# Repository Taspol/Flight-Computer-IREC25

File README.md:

## Link for Pin out Stm32Cube IDE
- https://drive.google.com/drive/folders/1xgfmS8LAHjObwQE3LNUNcHKHxMRXHLm3?usp=drive_link
# Flight Computer
## Overview
The Flight Computer is an embedded system designed for real-time data acquisition, processing, and communication in aerospace applications. It integrates multiple sensors and communication modules using an STM32 microcontroller, making it suitable for rocket flight.
## Features
**EnvSensor**
  - ADXL375BCCZ-RL7 (High-G Accelerometer)
  - BMI088 (Low-G Accelerometer & IMU Gyroscope)
  - MMC5983MA (Magnetometer)
  - TMP275AIDGKR VSSOP8 (OnBoard Temperature Sensors)
  - MS5607-02BA (Altimeter)

**Communication Modules**
  - SX1262 (Lora Module)

**Localization Modules**
  - SAM-M10Q (GNSS Module)

**Flight Data Storage**
  - KLM8G1GETF-B041(EMMC)

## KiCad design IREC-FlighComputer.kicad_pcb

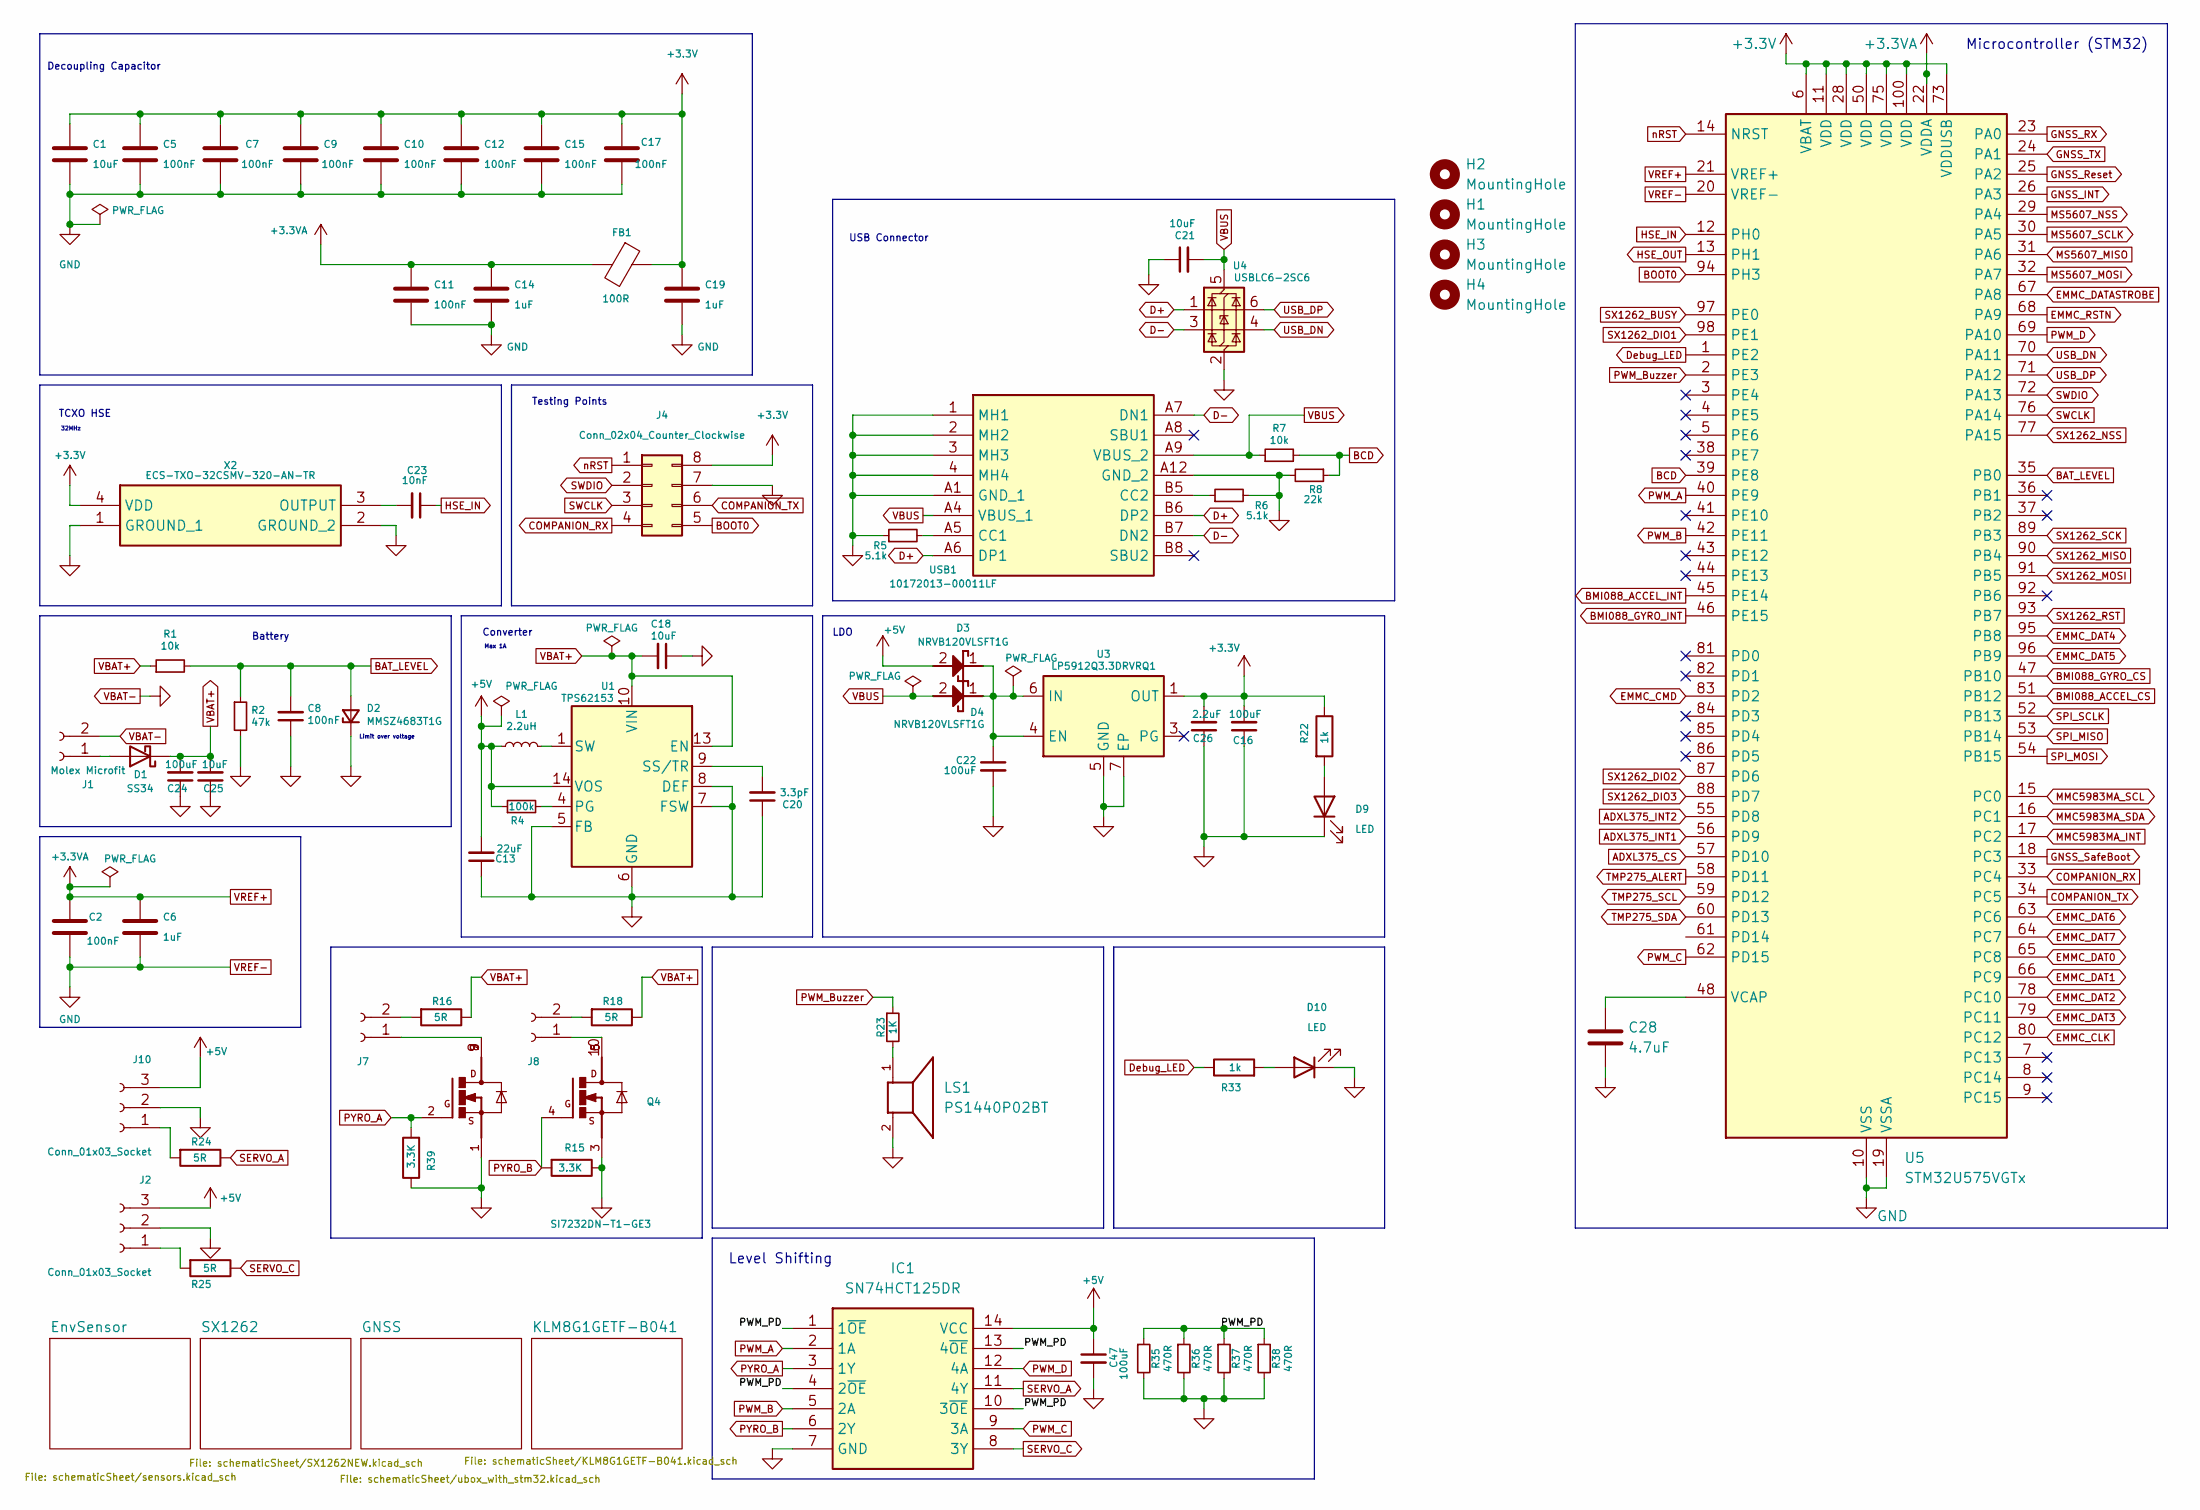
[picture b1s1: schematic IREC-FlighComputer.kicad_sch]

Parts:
C1, C18, C21, C25: 10uF; C_0402_1005Metric_Pad0.74x0.62mm_HandSolder
C2, C5, C7, C8, C9, C10, C11, C12, C15, C17: 100nF; C_0402_1005Metric_Pad0.74x0.62mm_HandSolder
C6, C14, C19: 1uF; C_0402_1005Metric_Pad0.74x0.62mm_HandSolder
C13: 22uF; C_0402_1005Metric_Pad0.74x0.62mm_HandSolder
C16, C22, C24, C47: 100uF; C_0402_1005Metric_Pad0.74x0.62mm_HandSolder
C20: 3.3pF; C_0402_1005Metric_Pad0.74x0.62mm_HandSolder
C23: 10nF; C_0402_1005Metric_Pad0.74x0.62mm_HandSolder
C26: 2.2uF; C_0402_1005Metric_Pad0.74x0.62mm_HandSolder
C28: 4.7uF; C_0402_1005Metric_Pad0.74x0.62mm_HandSolder
D1: SS34; DIOM7959X262N
D2: MMSZ4683T1G; SOD3716X135N; Manufacturer_Part_Number MMSZ4683T1G; Mouser Part Number 863-MMSZ4683T1G
D3, D4: NRVB120VLSFT1G; SODFL3616X98N; Manufacturer_Part_Number NRVB120VLSFT1G; Mouser 863-NRVB120VLSFT1G
D9, D10: LED; LED_0402_1005Metric
FB1: 100R; L_0603_1608Metric_Pad1.05x0.95mm_HandSolder
H1, H2, H3, H4: MountingHole; MountingHole_3.2mm_M3_DIN965_Pad
IC1: SN74HCT125DR; SOIC127P600X175-14N; Mouser Part Number 595-SN74HCT125DR
J1: Molex Microfit; Molex_Micro-Fit_3.0_43650-0215_1x02_P3.00mm_Vertical
J2, J10: Conn_01x03_Socket; Molex_Micro-Fit_3.0_43650-0315_1x03_P3.00mm_Vertical
J4: Conn_02x04_Counter_Clockwise; PinHeader_2x04_P2.54mm_Vertical
J7, J8: Conn_01x02_Socket; Molex_Micro-Fit_3.0_43650-0215_1x02_P3.00mm_Vertical
L1: 2.2uH; L_Coilcraft_XxL4020; Mouser 994-XFL4020-222MEC
LS1: PS1440P02BT; BUZZER_PS1440P02BT
Q4: SI7232DN-T1-GE3; TRANS_SI7232DN-T1-GE3
R1, R7: 10k; R_0402_1005Metric_Pad0.72x0.64mm_HandSolder
R2: 47k; R_0402_1005Metric_Pad0.72x0.64mm_HandSolder
R4: 100k; R_0402_1005Metric_Pad0.72x0.64mm_HandSolder
R5, R6: 5.1k; R_0402_1005Metric_Pad0.72x0.64mm_HandSolder
R8: 22k; R_0402_1005Metric_Pad0.72x0.64mm_HandSolder
R15, R39: 3.3K; R_0402_1005Metric
R16, R18, R24, R25: 5R; R_0402_1005Metric
R22, R33: 1k; R_0402_1005Metric
R23: 1K; R_0402_1005Metric_Pad0.72x0.64mm_HandSolder
R35, R36, R37, R38: 470R; R_0402_1005Metric_Pad0.72x0.64mm_HandSolder
U1: TPS62153; VQFN-16-1EP_3x3mm_P0.5mm_EP1.68x1.68mm_ThermalVias
U3: LP5912Q3.3DRVRQ1; WSON-6-1EP_2x2mm_P0.65mm_EP1x1.6mm_ThermalVias; Mouser 595-LP5912Q3.3DRVRQ1
U4: USBLC6-2SC6; SOT-23-6
U5: STM32U575VGTx; LQFP-100_14x14mm_P0.5mm
USB1: 10172013-00011LF; AMPHENOL_10172013-00011LF; Manufacturer_Part_Number 10172013-00011LF; LCSC Part C169130
X2: ECS-TXO-32CSMV-320-AN-TR; OSC_ECS-TXO-2520-33-320-AN-TR; Manufacturer_Part_Number ECS-TXO-32CSMV-320-AN-TR; Mouser Part Number 520-TXO32CSMV320ANTR

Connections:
+3.3V: C1.1, C5.1, C7.1, C9.1, C10.1, C12.1, C15.1, C16.2, C17.2, C19.1, C26.2, FB1.1, J4.8, R22.1, U3.1 (OUT), U5.6 (VBAT), U5.11 (VDD), U5.28 (VDD), U5.50 (VDD), U5.73 (VDDUSB), U5.75 (VDD), U5.100 (VDD), X2.4 (VDD); also elsewhere on the board
+5V: C13.2, C47.1, D3.2 (A), IC1.14 (VCC), J2.3, J10.3, L1.1, R4.1, U1.14 (VOS)
/PWM_PD: IC1.1 (1~OE), IC1.4 (2~OE), IC1.10 (3~OE), IC1.13 (4~OE), R35.1, R36.1, R37.1, R38.1
ADXL375_CS: U5.57 (PD10); also elsewhere on the board
ADXL375_INT1: U5.56 (PD9); also elsewhere on the board
ADXL375_INT2: U5.55 (PD8); also elsewhere on the board
BAT_LEVEL: C8.2, D2.A, R1.2, R2.1, U5.35 (PB0)
BCD: R7.2, R8.1, U5.39 (PE8)
BMI088_ACCEL_CS: U5.51 (PB12); also elsewhere on the board
BMI088_ACCEL_INT: U5.45 (PE14); also elsewhere on the board
BMI088_GYRO_CS: U5.47 (PB10); also elsewhere on the board
BMI088_GYRO_INT: U5.46 (PE15); also elsewhere on the board
BOOT0: J4.5, U5.94 (PH3)
COMPANION_RX: J4.4, U5.33 (PC4)
COMPANION_TX: J4.6, U5.34 (PC5)
D+: U4.1 (I/O1), USB1.A6 (DP1), USB1.B6 (DP2)
D-: U4.3 (I/O2), USB1.A7 (DN1), USB1.B7 (DN2)
Debug_LED: R33.1, U5.1 (PE2)
EMMC_CLK: U5.80 (PC12); also elsewhere on the board
EMMC_CMD: U5.83 (PD2); also elsewhere on the board
EMMC_DAT0: U5.65 (PC8); also elsewhere on the board
EMMC_DAT1: U5.66 (PC9); also elsewhere on the board
EMMC_DAT2: U5.78 (PC10); also elsewhere on the board
EMMC_DAT3: U5.79 (PC11); also elsewhere on the board
EMMC_DAT4: U5.95 (PB8); also elsewhere on the board
EMMC_DAT5: U5.96 (PB9); also elsewhere on the board
EMMC_DAT6: U5.63 (PC6); also elsewhere on the board
EMMC_DAT7: U5.64 (PC7); also elsewhere on the board
EMMC_DATASTROBE: U5.67 (PA8); also elsewhere on the board
EMMC_RSTN: U5.68 (PA9); also elsewhere on the board
GNSS_INT: U5.26 (PA3); also elsewhere on the board
GNSS_RX: U5.23 (PA0); also elsewhere on the board
GNSS_Reset: U5.25 (PA2); also elsewhere on the board
GNSS_SafeBoot: U5.18 (PC3); also elsewhere on the board
GNSS_TX: U5.24 (PA1); also elsewhere on the board
HSE_IN: C23.1, U5.12 (PH0)
HSE_OUT: U5.13 (PH1)
MMC5983MA_INT: U5.17 (PC2); also elsewhere on the board
MMC5983MA_SCL: U5.15 (PC0); also elsewhere on the board
MMC5983MA_SDA: U5.16 (PC1); also elsewhere on the board
MS5607_MISO: U5.31 (PA6); also elsewhere on the board
MS5607_MOSI: U5.32 (PA7); also elsewhere on the board
MS5607_NSS: U5.29 (PA4); also elsewhere on the board
MS5607_SCLK: U5.30 (PA5); also elsewhere on the board
unnamed: D1.2 (A), J1.1
unnamed: C22.1, D3.1 (K), D4.1 (K), U3.4 (EN), U3.6 (IN)
unnamed: D9.2 (A), R22.2
unnamed: D10.2 (A), R33.2
unnamed: J2.1, R25.2
unnamed: J7.1, Q4.7, Q4.8, Q4.9
unnamed: J7.2, R16.2
unnamed: J8.1, Q4.5, Q4.6, Q4.10
unnamed: J8.2, R18.2
unnamed: J10.1, R24.2
unnamed: L1.2, U1.1 (SW), U1.2 (SW), U1.3 (SW)
unnamed: LS1.1, R23.2
unnamed: R4.2, U1.4 (PG)
unnamed: C20.2, U1.9 (SS/TR)
unnamed: C28.1, U5.48 (VCAP)
unnamed: R5.2, USB1.A5 (CC1)
unnamed: R6.1, USB1.B5 (CC2)
unnamed: C23.2, X2.3 (OUTPUT)
PWM_A: IC1.2 (1A), U5.40 (PE9)
PWM_B: IC1.5 (2A), U5.42 (PE11)
PWM_Buzzer: R23.1, U5.2 (PE3)
PWM_C: IC1.9 (3A), U5.62 (PD15)
PWM_D: IC1.12 (4A), U5.69 (PA10)
PYRO_A: IC1.3 (1Y), Q4.2, R39.2
PYRO_B: IC1.6 (2Y), Q4.4, R15.2
SERVO_A: IC1.11 (4Y), R24.1
SERVO_C: IC1.8 (3Y), R25.1
SWCLK: J4.3, U5.76 (PA14)
SWDIO: J4.2, U5.72 (PA13)
SX1262_BUSY: U5.97 (PE0); also elsewhere on the board
SX1262_DIO1: U5.98 (PE1); also elsewhere on the board
SX1262_DIO2: U5.87 (PD6)
SX1262_DIO3: U5.88 (PD7); also elsewhere on the board
SX1262_MISO: U5.90 (PB4); also elsewhere on the board
SX1262_MOSI: U5.91 (PB5); also elsewhere on the board
SX1262_NSS: U5.77 (PA15); also elsewhere on the board
SX1262_RST: U5.93 (PB7); also elsewhere on the board
SX1262_SCK: U5.89 (PB3); also elsewhere on the board
TMP275_ALERT: U5.58 (PD11); also elsewhere on the board
TMP275_SCL: U5.59 (PD12); also elsewhere on the board
TMP275_SDA: U5.60 (PD13); also elsewhere on the board
USB_DN: U4.4 (I/O2), U5.70 (PA11)
USB_DP: U4.6 (I/O1), U5.71 (PA12)
VBAT+: C18.2, C24.2, C25.2, D1.1 (K), R1.1, R16.1, R18.1, U1.10 (VIN), U1.11 (VIN), U1.12 (VIN), U1.13 (EN)
VBAT-: C1.2, C2.2, C5.2, C6.2, C7.2, C8.1, C9.2, C10.2, C11.2, C12.2, C13.1, C14.2, C15.2, C16.1, C17.1, C18.1, C19.2, C20.1, C21.1, C22.2, C24.1, C25.1, C26.1, C28.2, C47.2, D2.C, D9.1 (K), D10.1 (K), IC1.7 (GND), J1.2, J2.2, J4.7, J10.2, LS1.2, Q4.1, Q4.3, R2.2, R5.1, R6.2, R8.2, R15.1, R35.2, R36.2, R37.2, R38.2, R39.1, U1.5 (FB), U1.6 (GND), U1.7 (FSW), U1.8 (DEF), U1.15 (GND), U1.16 (GND), U1.17 (GND), U3.5 (GND), U3.7 (EP), U4.2 (GND), U5.10 (VSS), U5.19 (VSSA), U5.20 (VREF-), U5.27 (VSS), U5.49 (VSS), U5.74 (VSS), U5.99 (VSS), USB1.1 (MH1), USB1.2 (MH2), USB1.3 (MH3), USB1.4 (MH4), USB1.A1 (GND_1), USB1.A12 (GND_2), X2.1 (GROUND_1), X2.2 (GROUND_2); also elsewhere on the board
VBUS: C21.2, D4.2 (A), R7.1, U4.5 (VBUS), USB1.A4 (VBUS_1), USB1.A9 (VBUS_2)
VREF+: C2.1, C6.1, C11.1, C14.1, FB1.2, U5.21 (VREF+), U5.22 (VDDA)
nRST: J4.1, U5.14 (NRST)

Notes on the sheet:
Microcontroller (STM32)
TCXO HSE
LDO
Testing Points
Battery
USB Connector
Level Shifting
Converter
Limit over voltage
32MHz
Max 1A
Decoupling Capacitor

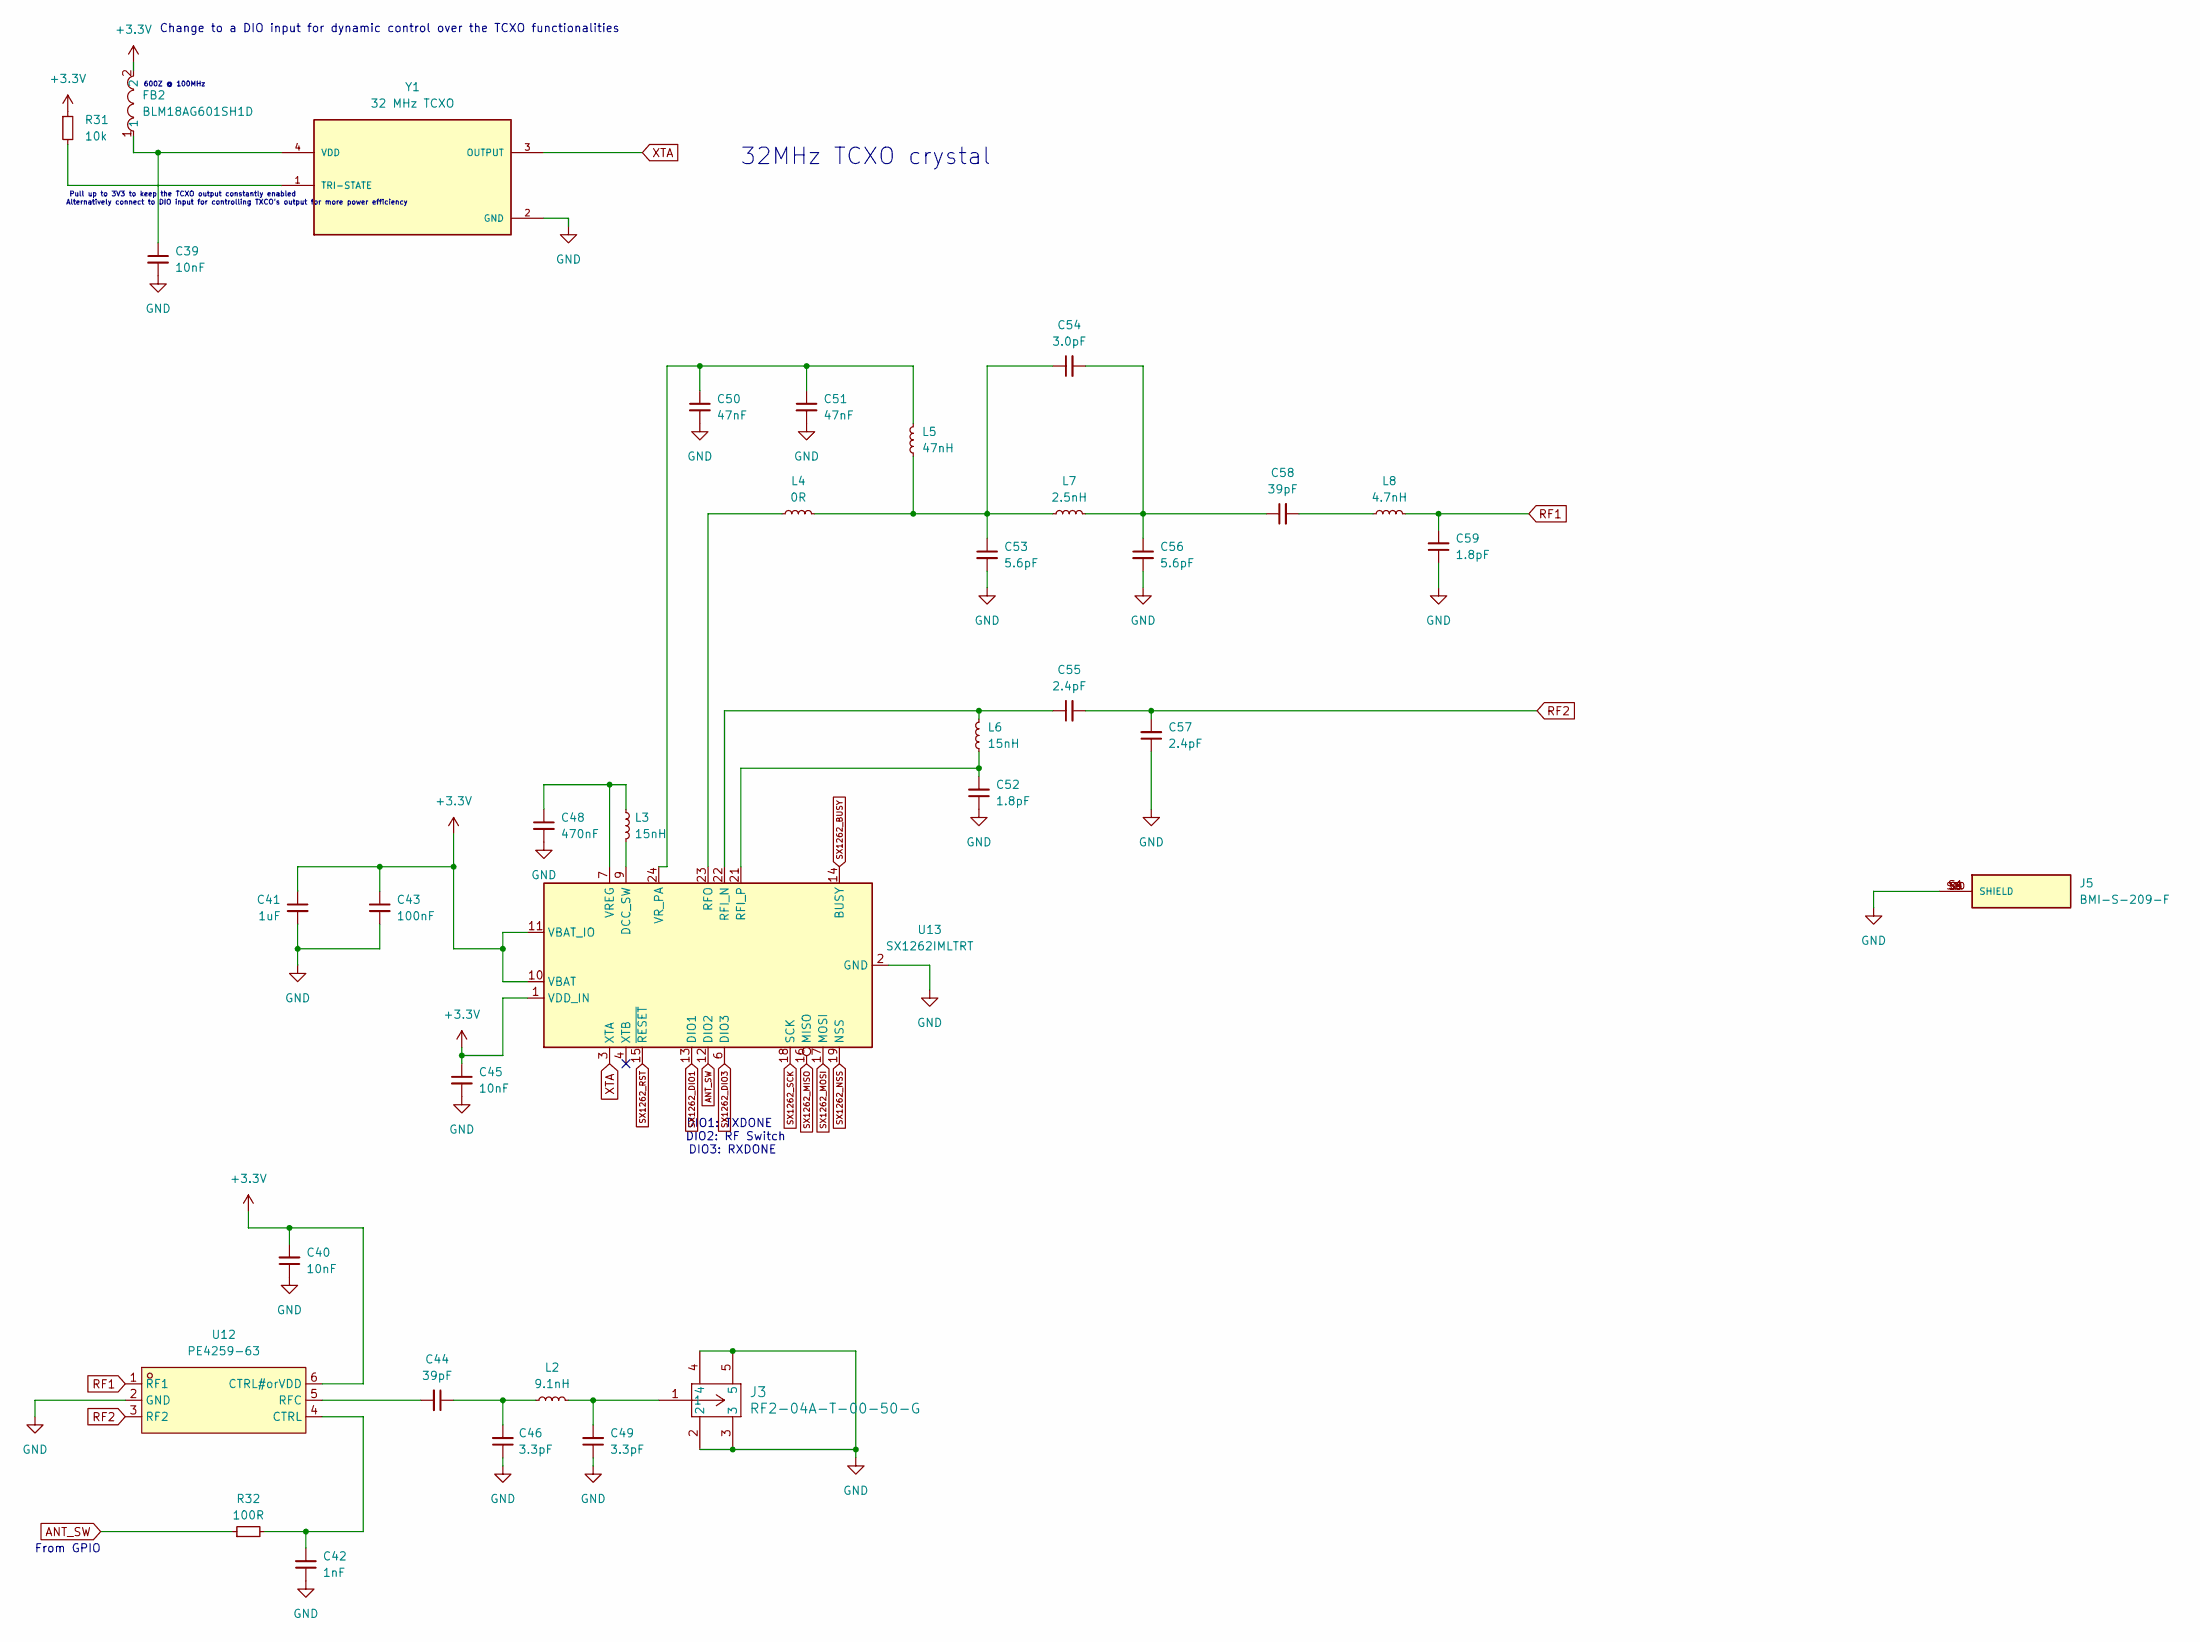
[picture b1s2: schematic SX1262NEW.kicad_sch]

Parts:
C39, C40, C45: 10nF; C_0402_1005Metric_Pad0.74x0.62mm_HandSolder
C41: 1uF; C_0402_1005Metric_Pad0.74x0.62mm_HandSolder
C42: 1nF; C_0402_1005Metric_Pad0.74x0.62mm_HandSolder
C43: 100nF; C_0402_1005Metric_Pad0.74x0.62mm_HandSolder
C44, C58: 39pF; C_0402_1005Metric_Pad0.74x0.62mm_HandSolder
C46, C49: 3.3pF; C_0402_1005Metric_Pad0.74x0.62mm_HandSolder
C48: 470nF; C_0402_1005Metric_Pad0.74x0.62mm_HandSolder
C50, C51: 47nF; C_0402_1005Metric_Pad0.74x0.62mm_HandSolder
C52, C59: 1.8pF; C_0402_1005Metric_Pad0.74x0.62mm_HandSolder
C53, C56: 5.6pF; C_0402_1005Metric_Pad0.74x0.62mm_HandSolder
C54: 3.0pF; C_0402_1005Metric_Pad0.74x0.62mm_HandSolder
C55, C57: 2.4pF; C_0402_1005Metric_Pad0.74x0.62mm_HandSolder
FB2: BLM18AG601SH1D; L0603; LCSC Part C73225
J3: RF2-04A-T-00-50-G; CONN_RF2-04A-T-00-50-G_ADM
J5: BMI-S-209-F; LAIRD_BMI-S-209-F; PARTREV N/A
L2: 9.1nH; L_0402_1005Metric
L3, L6: 15nH; L_0402_1005Metric
L4: 0R; L_0402_1005Metric
L5: 47nH; L_0402_1005Metric
L7: 2.5nH; L_0402_1005Metric
L8: 4.7nH; L_0402_1005Metric
R31: 10k; R_0402_1005Metric
R32: 100R; R_0402_1005Metric
U12: PE4259-63; SC-70-6_L2.2-W1.3-P0.65-LS2.1-BL; LCSC Part C470892
U13: SX1262IMLTRT; QFN-24-1EP_4x4mm_P0.5mm_EP2.6x2.6mm
Y1: 32 MHz TCXO; OSC_ECS-TXO-2520-33-320-AN-TR; PARTREV 2017

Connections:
+3.3V: C40.2, C41.1, C43.1, C45.1, FB2.2, R31.1, U12.6 (CTRL#orVDD), U13.1 (VDD_IN), U13.10 (VBAT), U13.11 (VBAT_IO); also elsewhere on the board
ANT_SW: R32.1, U13.12 (DIO2)
unnamed: C44.1, C46.2, L2.1
unnamed: C49.2, J3.1, L2.2
unnamed: C53.1, C54.1, L4.2, L5.1, L7.1
unnamed: C54.2, C56.1, C58.1, L7.2
unnamed: C58.2, L8.1
unnamed: C42.2, R32.2, U12.4 (CTRL)
unnamed: C44.2, U12.5 (RFC)
unnamed: L3.2, U13.9 (DCC_SW)
unnamed: C55.1, L6.2, U13.22 (RFI_N)
unnamed: C52.2, L6.1, U13.21 (RFI_P)
unnamed: L4.1, U13.23 (RFO)
unnamed: C48.1, L3.1, U13.7 (VREG)
unnamed: C50.1, C51.1, L5.2, U13.24 (VR_PA)
unnamed: R31.2, Y1.1 (TRI-STATE)
unnamed: C39.1, FB2.1, Y1.4 (VDD)
RF1: C59.2, L8.2, U12.1 (RF1)
RF2: C55.2, C57.2, U12.3 (RF2)
SX1262_BUSY: U13.14 (BUSY); also elsewhere on the board
SX1262_DIO1: U13.13 (DIO1); also elsewhere on the board
SX1262_DIO3: U13.6 (DIO3); also elsewhere on the board
SX1262_MISO: U13.16 (MISO); also elsewhere on the board
SX1262_MOSI: U13.17 (MOSI); also elsewhere on the board
SX1262_NSS: U13.19 (NSS); also elsewhere on the board
SX1262_RST: U13.15 (~RESET); also elsewhere on the board
SX1262_SCK: U13.18 (SCK); also elsewhere on the board
VBAT-: C39.2, C40.1, C41.2, C42.1, C43.2, C45.2, C46.1, C48.2, C49.1, C50.2, C51.2, C52.1, C53.2, C56.2, C57.1, C59.1, J3.2, J3.3, J3.4, J3.5, J5.S1, J5.S3 (SHIELD), J5.S6 (SHIELD), J5.S9 (SHIELD), J5.S10 (SHIELD), U12.2 (GND), U13.2 (GND), U13.5 (GND), U13.8 (GND), U13.20 (GND), U13.25 (GND), Y1.2 (GND); also elsewhere on the board
XTA: U13.3 (XTA), Y1.3 (OUTPUT)

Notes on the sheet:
Change to a DIO input for dynamic control over the TCXO functionalities
Alternatively connect to DIO input for controlling TXCO's output for more power efficiency
600Z @ 100MHz
From GPIO
32MHz TCXO crystal
Pull up to 3V3 to keep the TCXO output constantly enabled
DIO1: TXDONE DIO2: RF Switch DIO3: RXDONE

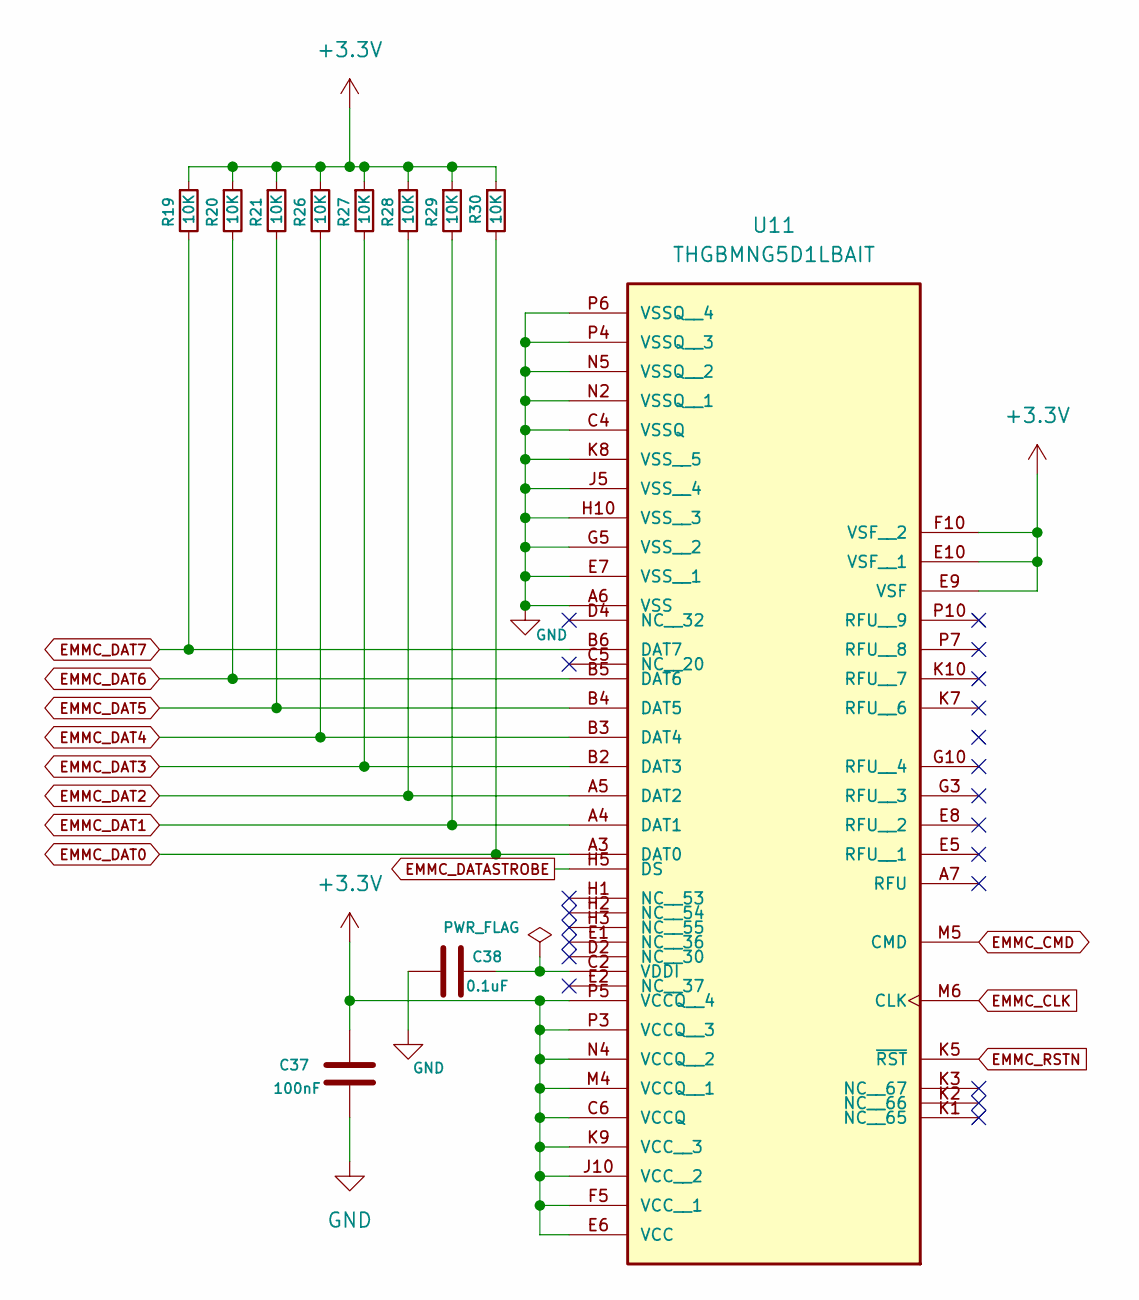
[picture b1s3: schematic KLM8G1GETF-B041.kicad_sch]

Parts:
C37: 100nF; C_0402_1005Metric_Pad0.74x0.62mm_HandSolder
C38: 0.1uF; C_0402_1005Metric_Pad0.74x0.62mm_HandSolder
R19, R20, R21, R26, R27, R28, R29, R30: 10K; R_0402_1005Metric
U11: THGBMNG5D1LBAIT; BGA-153_L13.0-W11.5-P0.50-TL_KLM8G1GEME-B041; PARTREV 1.0

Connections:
+3.3V: C37.1, R19.1, R20.1, R21.1, R26.1, R27.1, R28.1, R29.1, R30.1, U11.C6 (VCCQ), U11.E6 (VCC), U11.E9 (VSF), U11.E10 (VSF__1), U11.F5 (VCC__1), U11.F10 (VSF__2), U11.J10 (VCC__2), U11.K9 (VCC__3), U11.M4 (VCCQ__1), U11.N4 (VCCQ__2), U11.P3 (VCCQ__3), U11.P5 (VCCQ__4); also elsewhere on the board
EMMC_CLK: U11.M6 (CLK); also elsewhere on the board
EMMC_CMD: U11.M5 (CMD); also elsewhere on the board
EMMC_DAT0: R30.2, U11.A3 (DAT0); also elsewhere on the board
EMMC_DAT1: R29.2, U11.A4 (DAT1); also elsewhere on the board
EMMC_DAT2: R28.2, U11.A5 (DAT2); also elsewhere on the board
EMMC_DAT3: R27.2, U11.B2 (DAT3); also elsewhere on the board
EMMC_DAT4: R26.2, U11.B3 (DAT4); also elsewhere on the board
EMMC_DAT5: R21.2, U11.B4 (DAT5); also elsewhere on the board
EMMC_DAT6: R20.2, U11.B5 (DAT6); also elsewhere on the board
EMMC_DAT7: R19.2, U11.B6 (DAT7); also elsewhere on the board
EMMC_DATASTROBE: U11.H5 (DS); also elsewhere on the board
EMMC_RSTN: U11.K5 (~RST); also elsewhere on the board
unnamed: C38.2, U11.C2 (VDDI)
VBAT-: C37.2, C38.1, U11.A6 (VSS), U11.C4 (VSSQ), U11.E7 (VSS__1), U11.G5 (VSS__2), U11.H10 (VSS__3), U11.J5 (VSS__4), U11.K8 (VSS__5), U11.N2 (VSSQ__1), U11.N5 (VSSQ__2), U11.P4 (VSSQ__3), U11.P6 (VSSQ__4); also elsewhere on the board

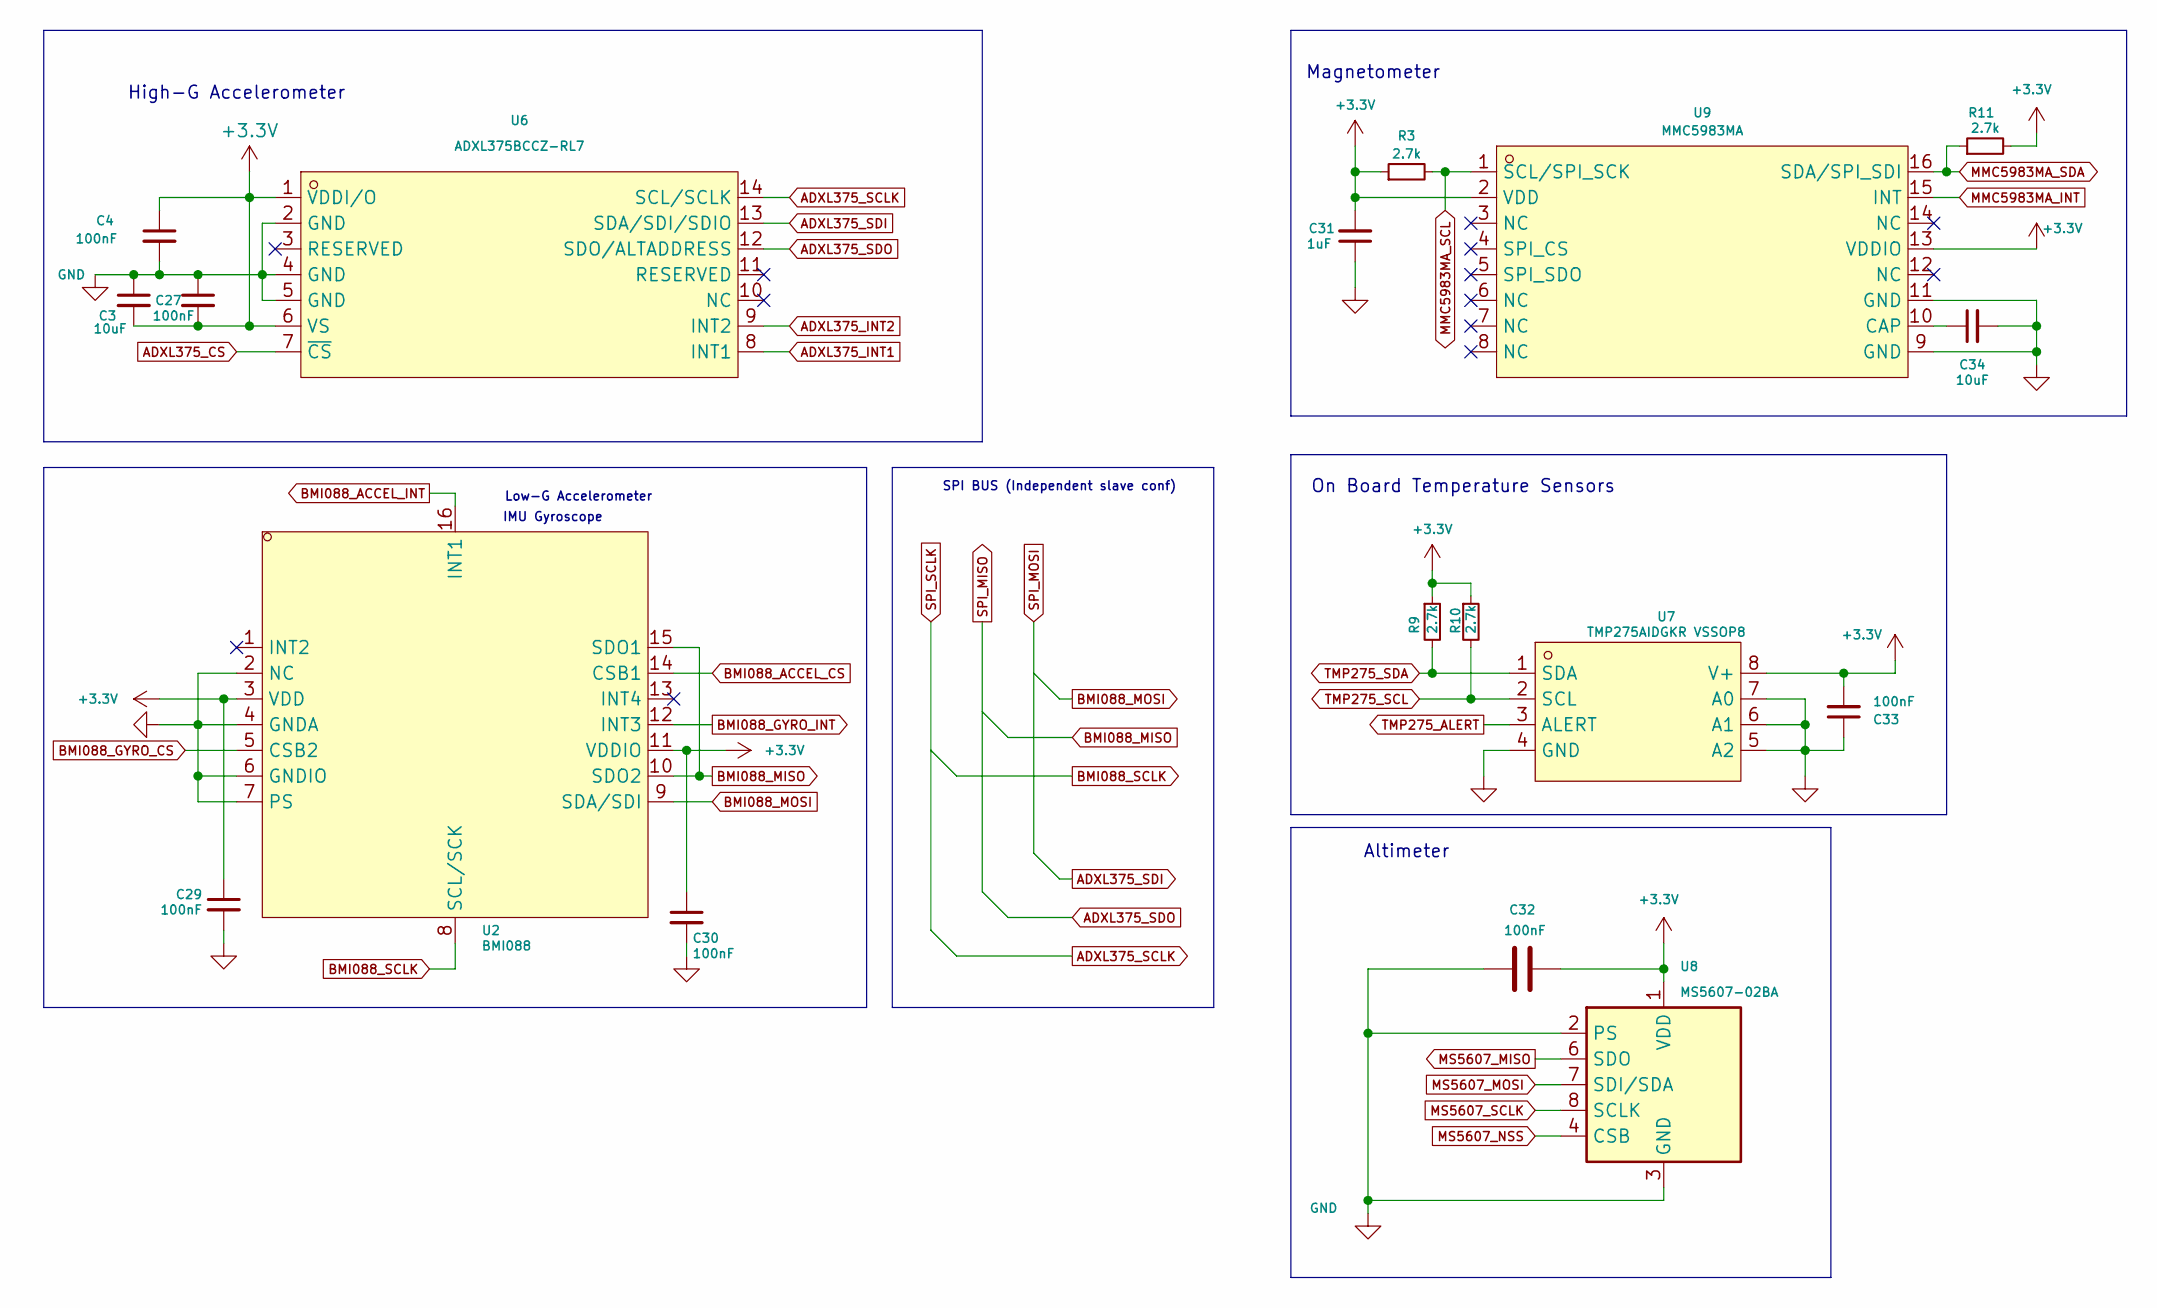
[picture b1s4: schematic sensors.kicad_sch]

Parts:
C3, C34: 10uF; C_0402_1005Metric_Pad0.74x0.62mm_HandSolder
C4, C27, C29, C30, C32, C33: 100nF; C_0402_1005Metric_Pad0.74x0.62mm_HandSolder
C31: 1uF; C_0402_1005Metric_Pad0.74x0.62mm_HandSolder
R3, R11: 2.7k; R_0402_1005Metric_Pad0.72x0.64mm_HandSolder
R9, R10: 2.7k; R_0402_1005Metric
U2: BMI088; LGA-16_L4.5-W3.0-P0.50-BL; LCSC Part C194919
U6: ADXL375BCCZ-RL7; LGA-14_L5.0-W3.0-P0.80-BL; LCSC Part C481898
U7: TMP275AIDGKR VSSOP8; VSSOP-8_L3.0-W3.0-P0.65-LS5.0-BL; LCSC Part C87815
U8: MS5607-02BA; LGA-8_3x5mm_P1.25mm
U9: MMC5983MA; LGA-16_L3.0-W3.0-P0.50-BL_SQ; LCSC Part C404329

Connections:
+3.3V: C3.2, C4.1, C27.2, C29.1, C30.1, C31.2, C32.2, C33.2, R3.1, R9.1, R10.1, R11.2, U2.3 (VDD), U2.11 (VDDIO), U6.1 (VDDI/O), U6.6 (VS), U7.8 (V+), U8.1 (VDD), U9.2 (VDD), U9.13 (VDDIO); also elsewhere on the board
ADXL375_CS: U6.7 (~CS); also elsewhere on the board
ADXL375_INT1: U6.8 (INT1); also elsewhere on the board
ADXL375_INT2: U6.9 (INT2); also elsewhere on the board
BMI088_ACCEL_CS: U2.14 (CSB1); also elsewhere on the board
BMI088_ACCEL_INT: U2.16 (INT1); also elsewhere on the board
BMI088_GYRO_CS: U2.5 (CSB2); also elsewhere on the board
BMI088_GYRO_INT: U2.12 (INT3); also elsewhere on the board
MMC5983MA_INT: U9.15 (INT); also elsewhere on the board
MMC5983MA_SCL: R3.2, U9.1 (SCL/SPI_SCK); also elsewhere on the board
MMC5983MA_SDA: R11.1, U9.16 (SDA/SPI_SDI); also elsewhere on the board
MS5607_MISO: U8.6 (SDO); also elsewhere on the board
MS5607_MOSI: U8.7 (SDI/SDA); also elsewhere on the board
MS5607_NSS: U8.4 (CSB), U8.5 (CSB); also elsewhere on the board
MS5607_SCLK: U8.8 (SCLK); also elsewhere on the board
unnamed: C34.1, U9.10 (CAP)
TMP275_ALERT: U7.3 (ALERT); also elsewhere on the board
TMP275_SCL: R10.2, U7.2 (SCL); also elsewhere on the board
TMP275_SDA: R9.2, U7.1 (SDA); also elsewhere on the board
VBAT-: C3.1, C4.2, C27.1, C29.2, C30.2, C31.1, C32.1, C33.1, C34.2, U2.2 (NC), U2.4 (GNDA), U2.6 (GNDIO), U2.7 (PS), U6.2 (GND), U6.4 (GND), U6.5 (GND), U7.4 (GND), U7.5 (A2), U7.6 (A1), U7.7 (A0), U8.2 (PS), U8.3 (GND), U9.9 (GND), U9.11 (GND); also elsewhere on the board

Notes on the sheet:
Altimeter
Low-G Accelerometer
On Board Temperature Sensors
Magnetometer
SPI BUS (Independent slave conf)
High-G Accelerometer
IMU Gyroscope

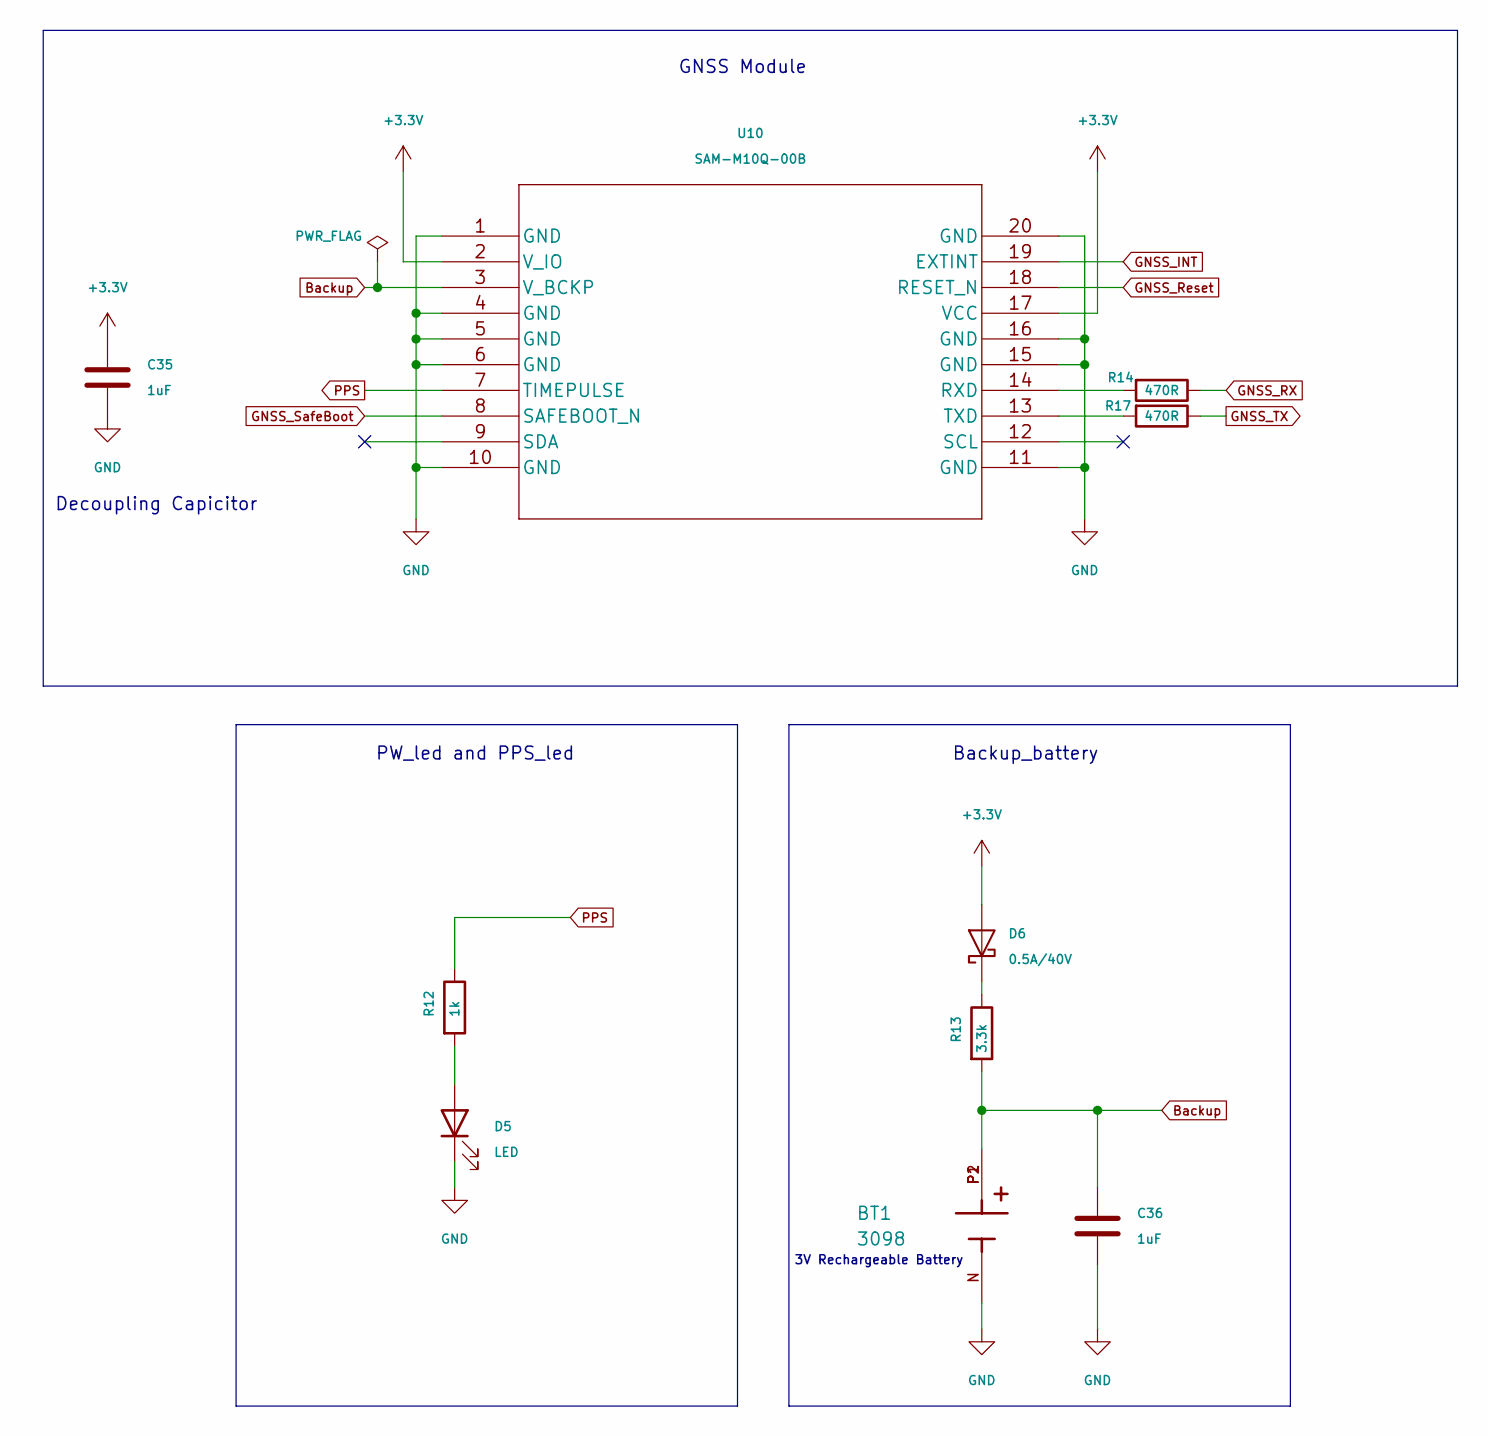
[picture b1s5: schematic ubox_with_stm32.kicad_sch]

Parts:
BT1: 3098; BAT_3098; PARTREV K
C35, C36: 1uF; C_0402_1005Metric_Pad0.74x0.62mm_HandSolder
D5: LED; LED_0402_1005Metric
D6: 0.5A/40V; D_SOD-123F
R12: 1k; R_0402_1005Metric
R13: 3.3k; R_0402_1005Metric
R14, R17: 470R; R_0402_1005Metric
U10: SAM-M10Q-00B; SAM-M10Q_UBL

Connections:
+3.3V: C35.1, D6.2 (A), U10.2 (V_IO), U10.17 (VCC); also elsewhere on the board
Backup: BT1.P1, BT1.P2, C36.1, R13.2, U10.3 (V_BCKP)
GNSS_INT: U10.19 (EXTINT); also elsewhere on the board
GNSS_RX: R14.1; also elsewhere on the board
GNSS_Reset: U10.18 (RESET_N); also elsewhere on the board
GNSS_SafeBoot: U10.8 (SAFEBOOT_N); also elsewhere on the board
GNSS_TX: R17.1; also elsewhere on the board
unnamed: D5.2 (A), R12.2
unnamed: D6.1 (K), R13.1
unnamed: R14.2, U10.14 (RXD)
unnamed: R17.2, U10.13 (TXD)
PPS: R12.1, U10.7 (TIMEPULSE)
VBAT-: BT1.N, C35.2, C36.2, D5.1 (K), U10.1 (GND), U10.4 (GND), U10.5 (GND), U10.6 (GND), U10.10 (GND), U10.11 (GND), U10.15 (GND), U10.16 (GND), U10.20 (GND); also elsewhere on the board

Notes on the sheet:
3V Rechargeable Battery
Backup_battery
GNSS Module
Decoupling Capicitor
PW_led and PPS_led

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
